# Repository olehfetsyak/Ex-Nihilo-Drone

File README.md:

# Drone v.0.0 Sim (Python)

by Mori

This stable simulator is **Sky Gadget No. 1: Euphrosyne Mirth Particle Windmill (name not final)**. The naming rules, such as they are, are in `NAMES.md`.

A flight simulator for our micro drone, laid out the same way as the software plan. `software-plan.png` is the original plan, and `software-plan_current.png` shows what is built today:

- **Drone**: ESP32-C3 Super Mini flight controller + Seeed Studio XIAO ESP32-S3 FPV camera
- **Macbook (Command Center)**: keyboard → Command Center → Safety Layer → Radio Bridge (ESP-NOW) → drone, with flight data and video coming back

You fly it with the keyboard, the same way the real Command Center will fly the drone. Every key is on a 65% board (we're using an Epomaker Magcore65 Lite), so no F-row or numpad is needed.

It is meant to feel like our first real flights, not like a game: the drone only knows what its IMU can tell it, the laptop only knows what the drone sends back, and the build is slightly imperfect.

## Run it

Needs Python 3.9 or newer. Tested on Python 3.9, 3.12 and 3.13 on Windows. It should run on macOS too, but that has not been tried yet.

```
pip install -r requirements.txt
python run_sim.py
```

Questions are answered in `FAQ.md`.

## Keys

| Key | Does |
|---|---|
| Enter | Arm. It never disarms |
| Space | DISARM (same as clicking the big red button) |
| W / S | Climb / descend. Let go to hover. First W after arming takes off |
| Q / E | Hover trim down / up 1%. Tap E if it sinks hands off, Q if it climbs |
| Arrows | Lean forward, back, left, right |
| A / D | Turn left / right |
| C | Camera: chase, drone camera (XIAO, with video delay), ground |
| L | Cut / restore the control link (tests the drone's failsafe) |
| T | Take control when the video is lost |
| V | Cut / restore the video (tests the safety layer's hover, then land) |
| 1 to 8 | Start a flight test (see below). 0 goes back to free flight |
| F | Full screen |
| R | Reset (or try the flight test again) |
| P | Pause |
| H | Show every key. The simulator waits while the panel is open |
| Esc | Quit |

The drone can't tell when it has landed. After you put it down with S the motors keep running until you disarm.

Arming needs both the link and the video. If the video drops in flight, the flight keys are locked out, the drone hovers, and the screen asks whether to take control. Press T and the keys are yours again without video. If nobody answers within `safety_hover_s` (5 s) it lands by itself; T still takes over during the landing. DISARM and Q/E always work.

## Flight tests

Press a number key to start one. Each shows pink rings to fly to and ends in PASS or FAIL. They run on top of whatever `--set` settings you started with, so you can fly the same test against a different build.

| Key | For | Test | To pass |
|---|---|---|---|
| 1 | hardware | Hover | Hover for 10 s: 0.5 to 2 m up, within 1.5 m of the pad, slower than 0.8 m/s. Tells you the hover throttle of this build |
| 2 | hardware | Weak battery | Battery at 25%: climb to 3 m and land softly without a brownout |
| 3 | hardware | Crooked build | Board 3° off level, motors 8% apart: stay within 2 m of the pad for 10 s |
| 4 | hardware | Breeze | 2 m/s wind with 0.5 m/s gusts: stay within 3 m of the pad for 10 s |
| 5 | software | Link drop | The link drops for 3 s once you are hovering above 4 m: take it back from the failsafe and land softly |
| 6 | software | Video drop | The video drops for good as you cross the ring at more than 2 m/s: take control (T) or let it land itself, softly |
| 7 | software | Lag | Commands 60 ms late, video 350 ms late: land inside the ring |
| 8 | software | Lost packets | 85% of packets lost both ways: land inside the ring |

The clock only runs while every condition is met, and the panel says what is missing when it isn't. A soft landing is a touchdown under 1.8 m/s, and a landing test only ends once you disarm. Some to try:

```
python run_sim.py --set mass_g=60                  # then 1: a heavier build needs E, and about 65% throttle
python run_sim.py --set regulator=ams1117          # then 2: fails with a brownout
python run_sim.py --set safety_hover_s=1           # then 6: it only waits 1 s for you before landing
python run_sim.py --tests                          # list them
```

## What to expect when flying

These come straight from test flights in the simulator, and the real drone should do the same:

- **It never sits still.** Hands off, it drifts sideways at around 0.1 m/s, because the board is never mounted dead level and the motors never match. There is nothing on the drone that can see the drift.
- **Hover is a guess.** The laptop holds one throttle number (`hover_throttle`) when you let go of W and S. If the real drone is 5 g heavier than we thought, it sinks back to the floor hands off; 5 g lighter and it climbs at about 1 m/s. Q and E fix it in flight. Measuring the real hover throttle is the first job.
- **Leaning forward loses height.** In fast forward flight it sinks slowly and needs taps of W.
- **Lean angle is the speed limit.** About 2.8 m/s with a 16° limit, 4.8 m/s with 32°. The real lean ends up a degree or two more than asked while it speeds up, because the accelerometer can't tell leaning from accelerating. `safety_max_tilt` (default 30°) is the only speed limit there is.
- **The battery sags.** Around 3.5 minutes of hovering on 300 mAh, and the throttle needed to hover goes from about 60% to almost 80% by the end.
- **Link lost.** The drone levels out, holds `failsafe_throttle`, comes down at about 1.6 m/s (about 3 m/s on a 25% battery, which is a hard landing), and cuts the motors after `failsafe_land_s` seconds whether or not it has reached the floor.
- **Video lost.** The flight keys stop working. The safety layer levels the drone, holds hover throttle and asks whether to take control (T); after 5 s with no answer it eases the drone down at about 1 m/s. It can't brake: from 4 m/s it coasts about 6 m before drag slows it to a crawl.
- **Low battery.** "LOW BATTERY" shows when the battery drops under 3.4 V in flight, with about 45 seconds of hover left.

## Change the drone

Settings match the real parts and change as parts get picked. Pass them with `--set`:

```
python run_sim.py --set regulator=ams1117          # watch it brown out on takeoff
python run_sim.py --set mass_g=60                  # built heavier than planned: needs E to hover
python run_sim.py --set hover_throttle=0.63        # the laptop's hover guess, once we've measured it
python run_sim.py --set level_error_deg=0 --set motor_mismatch=0   # a perfect build, for comparison
python run_sim.py --set safety_max_tilt=15         # gentler: lower lean and speed limit
python run_sim.py --set safety_hover_s=2           # video lost: wait 2 s for the pilot before landing
python run_sim.py --set wind=2
python run_sim.py --set video_loss=40               # stuttering video: 40% of frames never arrive
python run_sim.py --seed 1234                       # fly drone 1234 again
python run_sim.py --list                            # every setting, its default and its allowed range
```

A value outside the allowed range is refused with a message instead of starting.

Each launch is a different drone: the motor mismatch, the tilt of the board and the gyro bias are drawn fresh. The drone's number is in the window title and the H panel, and `--seed` with that number flies the same one again. The flight tests always use their own fixed drone.

The main ones are `chip` (c3, s3, esp32), `loop_hz`, `mass_g`, `motor_thrust_g`, `battery_mah`, `regulator` (ldo, ams1117, buckboost), `failsafe` (land, drop), `failsafe_throttle`, `link_delay_ms`, `link_loss`, `video_delay_ms`, `video_loss`, `cam_tilt`, `wind`, `gust` (both in m/s), `hover_throttle`, `safety_max_tilt`, `safety_hover_s`.

## Flight tuning

`--tune` flies a build through a fixed routine without a window (take off, hold 2 m, a sudden half-stick roll, a sudden half-stick turn) and prints how it responded, next to the default build:

```
python run_sim.py --tune --set p_roll=60 --set d_roll=40
```

| Line | What it tells you |
|---|---|
| hover throttle | The throttle this build hovers at, and the value to put in `hover_throttle` |
| hover wobble | How much it shakes hands off. More than a few deg/s means P or D is too high, or there is too much delay |
| motor spread | How far apart the motors are driven in the hover. A big spread means noise is getting through and the motors run hot |
| roll step | How fast it reaches a new lean, and how far it overshoots |
| yaw step | How fast it reaches a new turn rate |
| flight loop load | Whether the chip keeps up with `loop_hz` |

The tuning settings are `p_roll`, `i_roll`, `d_roll` (roll and pitch share them), `p_yaw`, `i_yaw`, `angle_gain`, `max_rate`, `yaw_rate`, `gyro_lpf`, `dterm_lpf` and `loop_hz`.

How far to trust it:

- Put the real build in first: `mass_g`, `motor_thrust_g` (thrust per motor), `arm_mm`, `battery_mah`. With guessed numbers the report describes a guessed drone.
- Use it to learn which way each value pushes and what bad tuning looks like, not to copy gains onto the drone. The simulator is more forgiving than real life: there is no frame flex, prop wash or bent prop.
- The gain numbers are on the simulator's own scale. They have not been checked against ESP-FC or Betaflight, so 45 here is not promised to be 45 there.

## What's simulated

### Drone side
- Physics at 4 kHz: thrust from motor speed squared, motor and ESC lag, drag, wind and gusts, ground contact and crashes
- An imperfect build: motors a few percent apart, the flight controller board about a degree off level
- Battery: voltage sag under load, the 3.3 V regulator, and brownout resets of the flight controller
- Flight controller like ESP-FC / Betaflight: gyro calibration, noisy gyro and accelerometer with motor vibration, filters, attitude estimate, self-levelling, rate PID, mixer with airmode, arming checks
- Failsafe like Betaflight's landing mode: level, fixed throttle, motors off after a set time
- Chip load: a slow chip can't run the flight loop as fast as asked
- XIAO camera view with video delay, frame rate and lost frames

### Command Center side
- **Radio Bridge**: ESP-NOW commands up and flight data down, each with packet rate, delay and loss
- **Flight data**: only what the drone can sense with the LSM6DSM: lean angles, battery voltage, armed. No height, speed or position
- **Command Center**: live video, flight data, link and video health, the big DISARM button
- **Safety Layer**: every command passes through it before the bridge
  - tilt limit (which is also the speed limit)
  - video lost → flight keys locked out, level out and hover, ask the pilot; no answer → land
  - the pilot always overrides: T takes control back, DISARM always works
  - link lost → the drone's own failsafe flies; the laptop keeps sending a calm hover command for when the link returns
  - no arming without both the link and the video
  - low battery warning

On screen, anything marked "sim only" (height, speed, CPU load, the pointer to the pad) is something the real Command Center won't have.

Not in the simulator: the AI and session recording from the plan.

## Later: the AI box

Three placeholders in `experiments/` hold notes only, and the simulator doesn't use any of them:

- `AI_brain.py`: the plan's AI (a small vision network, gestures, follow me), what it is given and what has to be built first.
- `fly_brain.py`: a separate mode with a real fruit fly brain in the same place, trained in this simulator.
- `indoor/indoor_place.py`: a room to fly in, with walls and a ceiling, instead of the open field.

## Command flow

```
Keyboard → pilot → Safety Layer → Radio Bridge (ESP-NOW) → Drone
                        ↑                                     |
                        └──────── flight data, video ─────────┘
```

## Files

The hardware side has its own folder and its own guide, `drone_sim/hardware/README.md`.

```
run_sim.py                     window, keys, and main loop

drone_sim/hardware/            the drone (hardware side)
  parts.py                     the build: every part setting, its default and allowed range
  drone.py                     physics, battery, flight controller, radio link (no graphics)
  flight_tests.py              flight tests 1 to 4
  tuning.py                    the --tune report
  README.md                    guide to this folder

drone_sim/                     the laptop (software side)
  __init__.py                  the name of this stable simulator
  command_center.py            laptop side, wired like the plan
  pilot.py                     keyboard -> stick values
  safety.py                    safety layer: tilt limit, hover or land
  video.py                     video link: delay, frame rate, dropouts
  flight_tests.py              runs the flight tests, and holds tests 5 to 8
  params.py                    laptop and weather settings, joined with the build
  view.py                      3D view and HUD (pygame)
  world.py                     obstacles
  quat.py                      quaternion math

tests/test_sim.py              flight checks that run without a window
tools/                         deeper checks: stress test, settings sweep, live window test (see tools/README.md)
FAQ.md                         common questions
NAMES.md                       how stable simulators are named
software-plan.png              the original plan
software-plan_current.png      the plan as built today
experiments/AI_brain.py        placeholder for the plan's AI (notes only)
experiments/fly_brain.py       placeholder for the fly brain mode (notes only)
experiments/indoor/            placeholder for an indoor place to fly (notes only)
```

## Tests

```
python tests/test_sim.py
```

That is the everyday check. `tools/` holds the deeper ones (random-input stress test, settings sweep, a live window test with real key presses); `tools/README.md` lists them.

## Notes

- Numbers like motor thrust, battery resistance, drag and chip loop cost are estimates until we measure the real parts. The drag guess is probably too high, so the real drone will likely fly and fall faster than this one; `drag_area_cm2` and `drag_linear` are the settings to correct.
- Tested with pygame 2.6.1, which is the version `requirements.txt` installs.
- All rights reserved. You're welcome to read the code; ask us before using or sharing it.
- The plan's Safety Layer has a speed limit and a hover-or-land fallback. With only an IMU the drone can't measure speed or height, so here the speed limit is a tilt limit and "hover" drifts. Doing either properly needs another sensor, such as optical flow with a range sensor.

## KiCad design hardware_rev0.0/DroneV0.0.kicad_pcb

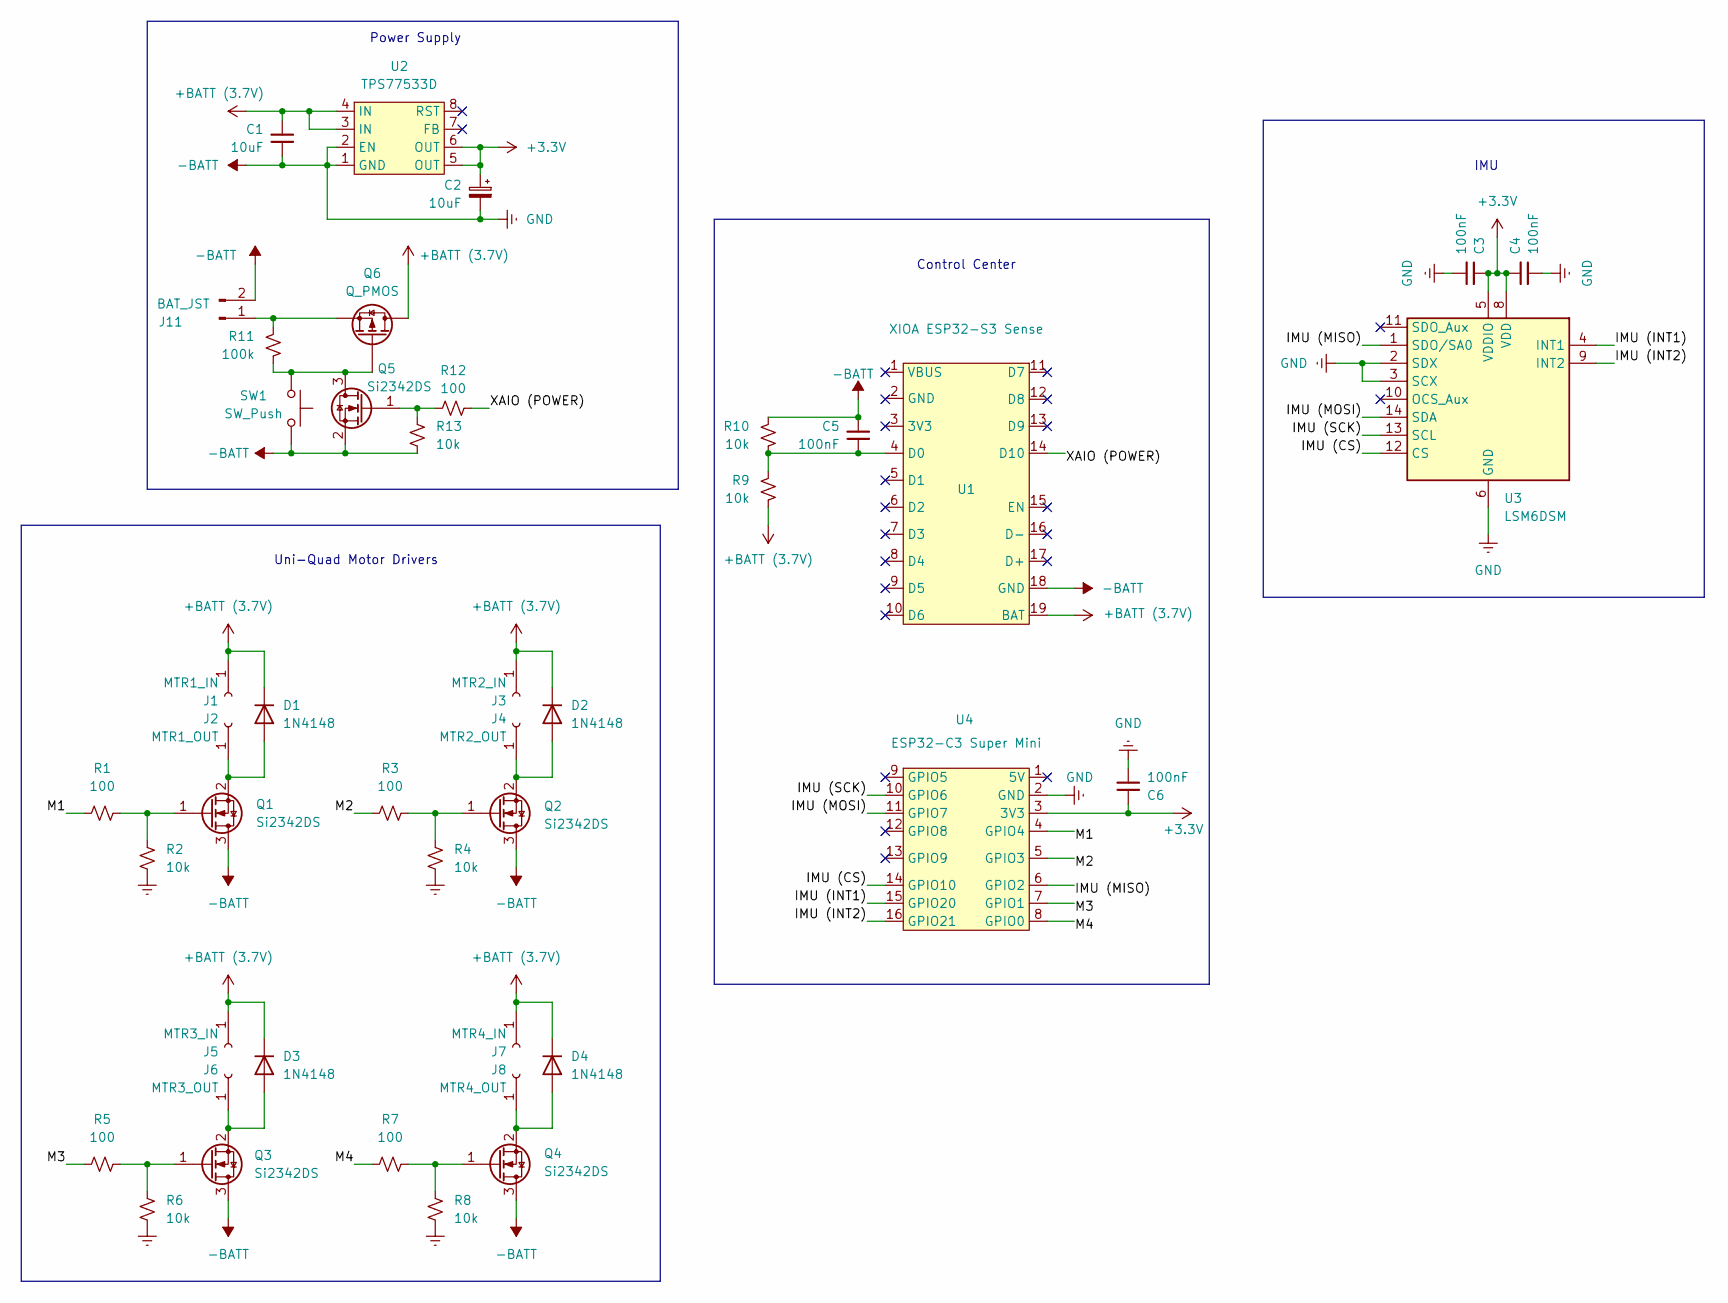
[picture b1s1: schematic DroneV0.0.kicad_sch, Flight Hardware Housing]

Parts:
C1: 10uF; C_0805_2012Metric
C2: 10uF; CP_EIA-2012-12_Kemet-R
C3, C4, C5, C6: 100nF; C_0805_2012Metric
D1, D2, D3, D4: 1N4148; D_SOD-123
J1: MTR1_IN; SolderWire-0.1sqmm_1x01_D0.4mm_OD1mm
J2: MTR1_OUT; SolderWire-0.1sqmm_1x01_D0.4mm_OD1mm
J3: MTR2_IN; SolderWire-0.1sqmm_1x01_D0.4mm_OD1mm
J4: MTR2_OUT; SolderWire-0.1sqmm_1x01_D0.4mm_OD1mm
J5: MTR3_IN; SolderWire-0.1sqmm_1x01_D0.4mm_OD1mm
J6: MTR3_OUT; SolderWire-0.1sqmm_1x01_D0.4mm_OD1mm
J7: MTR4_IN; SolderWire-0.1sqmm_1x01_D0.4mm_OD1mm
J8: MTR4_OUT; SolderWire-0.1sqmm_1x01_D0.4mm_OD1mm
J11: BAT_JST; PinHeader_1x02_P2.54mm_Vertical
Q1, Q2, Q3, Q4, Q5: Si2342DS; SOT-23
Q6: Q_PMOS; SOT-23
R1, R3, R5, R7, R12: 100; R_0805_2012Metric
R2, R4, R6, R8, R9, R10, R13: 10k; R_0805_2012Metric
R11: 100k; R_0805_2012Metric
SW1: SW_Push; NANOT240AS
U1: XIOA ESP32-S3 Sense; Seeed Studio XIAO ESP32-S3 Sense
U2: TPS77533D; SOIC-8_3.9x4.9mm_P1.27mm
U3: LSM6DSM; LGA-14_3x2.5mm_P0.5mm_LayoutBorder3x4y
U4: ESP32-C3 Super Mini

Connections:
+3.3V: C2.1, C3.1, C4.1, C6.1, U2.5 (OUT), U2.6 (OUT), U3.5 (VDDIO), U3.8 (VDD), U4.3 (3V3)
+BATT (3.7V): C1.1, D1.1 (K), D2.1 (K), D3.1 (K), D4.1 (K), J1.1 (Pin_1_1), J3.1 (Pin_1_1), J5.1 (Pin_1_1), J7.1 (Pin_1_1), Q6.3 (D), R9.2, U1.19 (BAT), U2.3 (IN), U2.4 (IN)
-BATT: C1.2, C2.2, C3.2, C4.2, C5.1, C6.2, J11.2, Q1.3 (D), Q2.3 (D), Q3.3 (D), Q4.3 (D), Q5.2 (S), R2.2, R4.2, R6.2, R8.2, R10.1, R13.2, SW1.2, U1.18 (GND), U2.1 (GND), U2.2 (EN), U3.2 (SDX), U3.3 (SCX), U3.6 (GND), U3.7 (GND), U4.2 (GND)
/IMU (CS): U3.12 (CS), U4.14 (GPIO10)
/IMU (INT1): U3.4 (INT1), U4.15 (GPIO20)
/IMU (INT2): U3.9 (INT2), U4.16 (GPIO21)
/IMU (MISO): U3.1 (SDO/SA0), U4.6 (GPIO2)
/IMU (MOSI): U3.14 (SDA), U4.11 (GPIO7)
/IMU (SCK): U3.13 (SCL), U4.10 (GPIO6)
/M1: R1.1, U4.4 (GPIO4)
/M2: R3.1, U4.5 (GPIO3)
/M3: R5.1, U4.7 (GPIO1)
/M4: R7.1, U4.8 (GPIO0)
/XAIO (POWER): R12.2, U1.14 (D10)
unnamed: D1.2 (A), J2.1 (Pin_1_1), Q1.2 (S)
unnamed: D2.2 (A), J4.1 (Pin_1_1), Q2.2 (S)
unnamed: D3.2 (A), J6.1 (Pin_1_1), Q3.2 (S)
unnamed: D4.2 (A), J8.1 (Pin_1_1), Q4.2 (S)
unnamed: J11.1, Q6.2 (S), R11.1
unnamed: Q1.1 (G), R1.2, R2.1
unnamed: Q2.1 (G), R3.2, R4.1
unnamed: Q3.1 (G), R5.2, R6.1
unnamed: Q4.1 (G), R7.2, R8.1
unnamed: Q5.3 (D), Q6.1 (G), R11.2, SW1.1
unnamed: Q5.1 (G), R12.1, R13.1
unnamed: C5.2, R9.1, R10.2, U1.4 (D0)

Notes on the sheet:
Control Center
Uni-Quad Motor Drivers
IMU
Power Supply

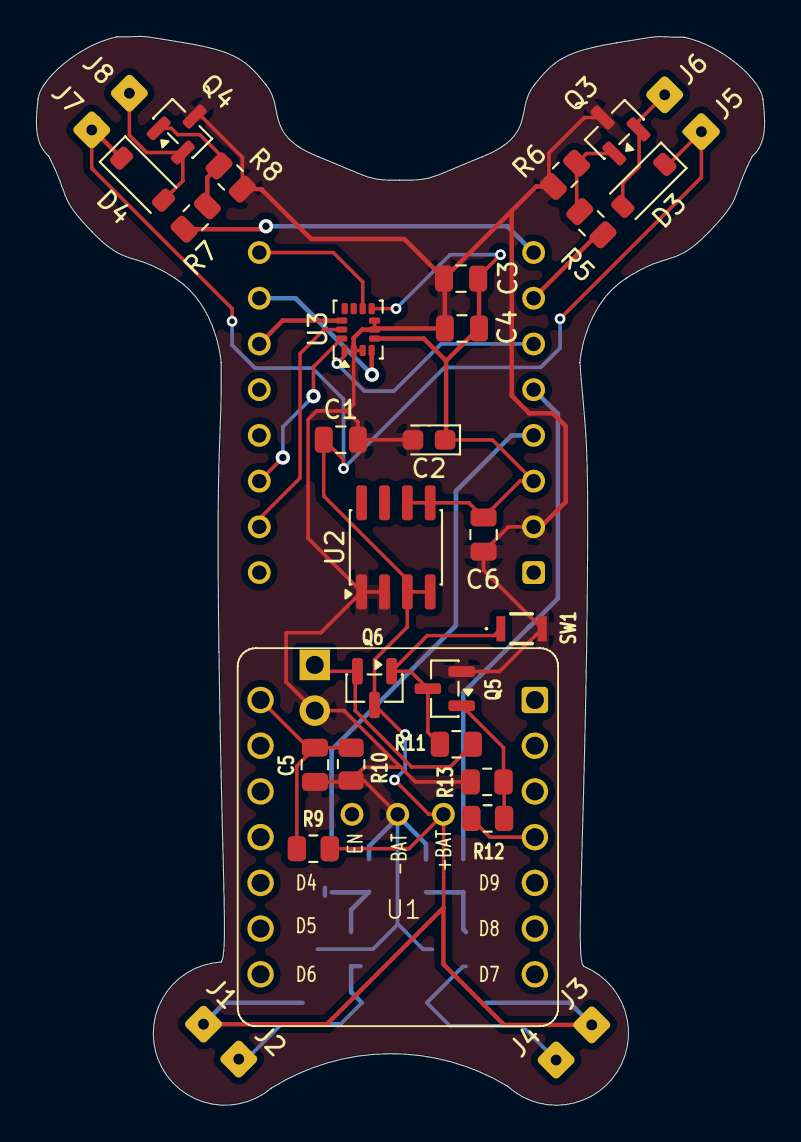
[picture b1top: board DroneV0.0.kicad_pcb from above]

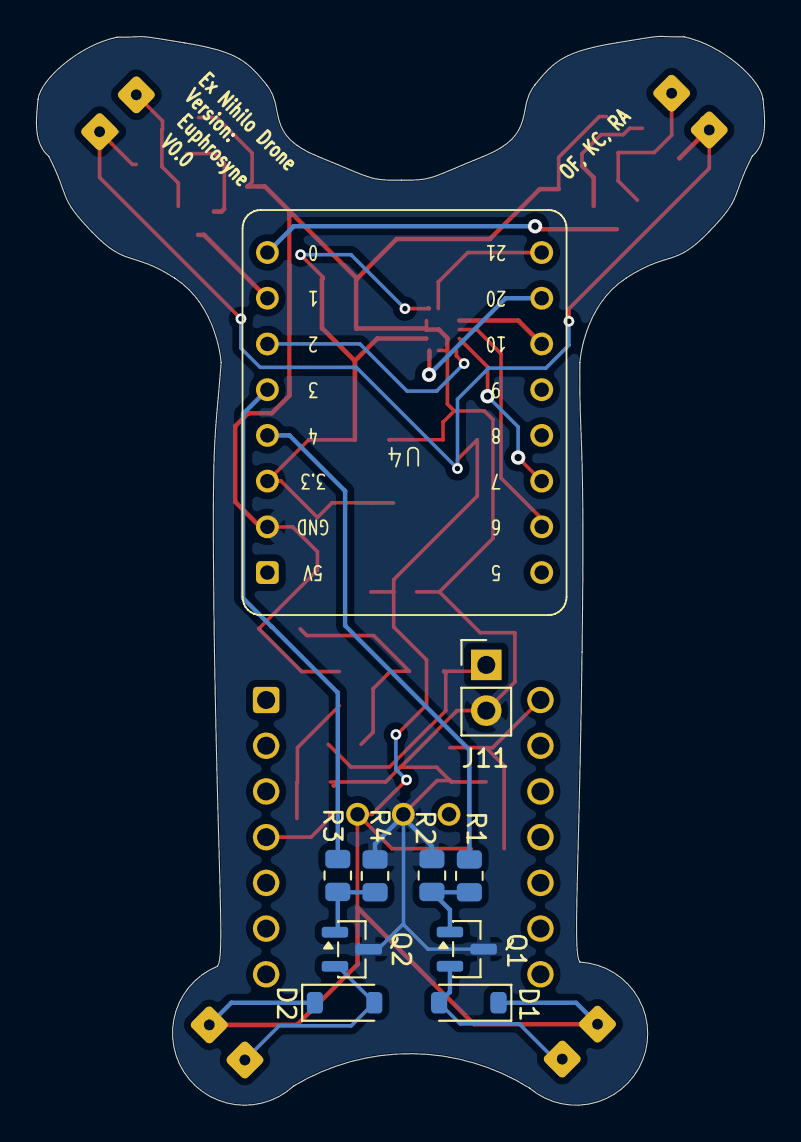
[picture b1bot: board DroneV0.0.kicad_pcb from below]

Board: 2 copper layers, 40.5 x 59.4 mm, 43 parts (10 on the bottom side), 26 nets.
